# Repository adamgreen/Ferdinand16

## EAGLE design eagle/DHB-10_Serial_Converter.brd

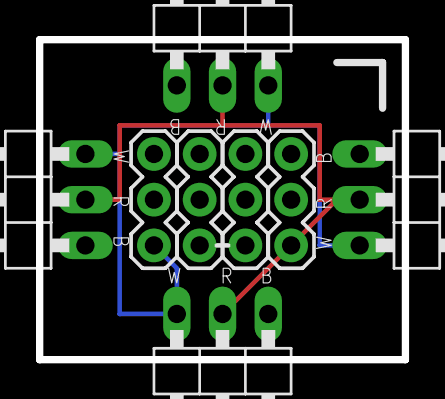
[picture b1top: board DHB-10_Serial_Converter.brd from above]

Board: 2 copper layers, 20.3 x 17.8 mm, 8 parts (0 on the bottom side), 2 nets.

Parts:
E$1, E$6, E$7, E$8: 1X03/90
E$2, E$3, E$4, E$5: 1X03

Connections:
S$1: E$1.3, E$2.1, E$6.3, E$7.3, E$8.3
S$2: E$1.2, E$5.1, E$6.2, E$7.2, E$8.2

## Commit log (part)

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2016-06-03 Initial commit
    * Add gcc4mbed as submodule since my firmware will make use of it.
    * Add initial photos.
    * The picture of the Arlo robot platform comes from the Parallax
    website.
    * The picture of the ESP8266 module comes from the Adafruit website.
2016-06-04 Add photo
    This is the graph of the gyro zero bias versus temperature from 2014.
2016-06-04 Initial README notes
    * Ideas for Robo-Magellan 2016 robot.
    * Initial Pixy camera notes.
    * Re-calibration of roll axis rate gyro in IMU.
2016-06-04 Add gyro calibration spreadhsheet
    This spreadsheet was used to re-calculate the gyro zero bias vs.
    temperature calibration constants.
2016-06-04 Fork orientation sample from Ferdinand14
    Just copying the orientation sample over from the Ferdinand14 project.
    This orientation code uses a Kalman filter to calculate the 3D pose of
    the IMU. I plan to simplify the code to just obtain the compass heading
    and then port to run on the LPC1768 instead of on the PC.
2016-06-06 Adding photos
2016-06-07 June 6th notes
2016-06-08 Add photo of new book
2016-06-09 Add photo of Sparkfun order
2016-06-11 June 10th notes
2016-06-12 Add ESP8266 board photos
2016-06-14 Calculate yaw from quaternion directly
    Previously I was using a row from the rotation matrix (which was
    more expensively obtained from the quaternion) and I now just pull the
    yaw, pitch, and roll angles from the quaternion instead.
2016-06-17 Start porting orientation code to LPC1768
    This is the start of porting the orientation Processing sample to the
    LPC1768. It just starts with porting of the calibration code down to
    the LPC1768 whereas it could only return the raw sensor readings
    previously.
    * The calibration data is found in files/config.ini This file it built
    into a FlashFileSystem image which is then embedded into the firmware
2016-06-18 Calculate orientation quaternion from accelerometer/magnetometer
    This commit switches the firmware to returning an orientation
    quaternion based soley on the accelerometer and magnetometer data.
    Kalman filtering will be added later.
    The orientation Processing sample was modified to expect this
    4 x float quaternion instead of the 9 x float calibrated data I added
    in the previous commit. It compares this quaternion to the one
2016-06-18 Swizzle accel/mag based on config.ini settings
    Previously the swizzling of the accelerometer and magnetometer axis was
    hardcoded. Now it is controlled by parameters in config.ini
    Additional changes include:
    * Added accelSwizzle and magSwizzle field to SensorCalibration struct
    to provide the new swizzle settings to the Sparkfun9DoFSensorStick
    class at construction time.
2016-06-21 Kalman filter ported to LPC1768
    This is the initial port of the Kalman filter from the Processing
    orientation.pde sample running on the PC to C++ code running on the
    LPC1768 microcontroller. The LPC1768 is currently idle for more than
    89% of the time when running this code. This is much better than I
    expected for all of that floating point math and gives me lots of
    headroom to execute my robot navigation code.
2016-06-21 Add Robo-Magellan June 19th photos
    These are photos taken at the June 19th, 2016 Robo-Magellan re-run
    event at Seattle Center.
2016-06-21 June 19th notes
    Notes about the Robo-Magellan 2015 rescheduled event.
2016-06-21 Add some photos
2016-06-21 Add animated GIF of Kalman filter
2016-06-21 June 20th notes
2016-06-22 Commit of quaternion and matrix dumping code
    I just want to keep this code around incase I want to reference it in
    the future. It is able to dump floats from various Kalman quaternions
    and matrices right after the filter is reset to compare the values
    between the PC and LPC1768.
    NOTE: It does contain a few fixes which I will port back into master as
    well.
2016-06-22 Kalman filter fixes
    * Make the Kalman filter reset a thread safe. Before it was possible
    for the code in main() which would trigger the Kalman filter
    to reset and the code which would prepend the "R," to the output
    would see different values of the g_resetRequested global that is
    set true in the serialRx ISR.
    * Sparkfun9DoFSensorStick::calibrate() gyroVariance & accelMagVariance
2016-06-23 PC and LPC1768 now agree on Kalman filter results
    I was normalizing the quaternion on the LPC1768 but not the PC. This is
    now fixed.
    I also fixed the code so that it only compares the embedded results
    after the reset has completed.
    Now get no differences detected when using a threshold of 1.0E-5.
2016-06-24 Add photo of Arlo
2016-06-25 June 24th notes
2016-06-28 June 28th notes
2016-07-12 July 11th notes
2016-07-12 Update README
    I wanted to make my comment about the 11% CPU utilization clearer. This
    was much better than I expected to obtain when I started the port.
2016-07-14 Commit some Parallax Arlo documentation
    * Documents for the DHB-10 Dual 10-Amp Motor Controller used on the
    Arlo robot platform for this Robo-Magellan bot. The LPC1768 will need
    to be interfaced to this motor controller in the near future.
    * The schematic for the power distribution board on the Arlo.
2016-07-14 Update compass/heading rendering
    I moved the code to calculate the compass heading from orientation.pde
    to HeadingSensor.pde This code was then updated to:
    * Return a heading angle of 0 when the robot is facing north.
    * Return a heading angle of PI/2 when the robot is facing east and
    an angle of -PI/2 when facing west.
    * Add configuration options to calibrate for the magnetic declination
2016-07-15 Start IMU firmware up in mode compatible with old samples
    The old Ferdinand14 samples like the ones I have for performing sensor
    calibration only expect the raw sensor readings. I have modified the
    firmware running on the LPC1768 to startup in a mode which only returns
    these raw sensor measurements and only starts returning the Kalman
    calculated values after a Kalman reset command has been sent from the
    PC.
2016-07-19 July 18th notes
2016-07-19 Move firmware & Processing code into sub-folders
    To support more than one Processing sample and firmware image for this
    project, there are now processing/ and firmware/ parent folders. The
    multiple Processing samples can be placed under processing/ and the
    different firmware images can be placed under firmware/.
    I also added the mriprog utility for OSX under the osx/ folder. This
    utility can be used to remotely program a LPC1768 device which is
2016-07-19 Build DmaSerial as a library
    I want to share the DmaSerial functionality between the basic heading
    firmware that I have been working on so far and the other firmware
    variants that I plan to create in the future. To facilitate this, I
    have moved the DMA code out into its own libs/DmaSerial directory. I
    also replaced DMA.h with GPDMA.h/c from my NeoPixelTree project where
    I added GPDMA channel allocation functionality. This will allow me to
2016-07-20 Add simple drive sample
    This sample instructs the Arlo platform to drive ahead at a speed of
    100 encoder ticks per second and verifies that the overall distance
    travelled (in encoder ticks) has increased as expected. This test is
    run for 2 seconds and then the robot is stopped.
    The bulk of the functionality is provided by the newly added
    libs/MotorController library which knows how to talk to the Parallax
2016-07-20 Add photos of completed Arlo build
    With Propeller board as the brains and another with the mbed LPC1768 as
    the brains.
2016-07-23 Move orientation sensor code into libraries
    I have moved the Sparkfun9DoFSensorStick code out into its own library
    so that it can be shared by the current Heading firmware and the new
    firmware for the robot itself. I also moved ConfigFile and
    FlashFileSystem out into their own libraries as well.
2016-07-23 Add photo
    Shows electronics to be combined inside of prototyping box.
2016-07-23 Add photo of merged electronics
2016-07-23 Add IMU sensor documentation
2016-07-23 Initial Ferdinand16 schematic
    I created a schematic in Eagle CAD to provide an overview of what
    electronics I am currently using for the brains of my Ferdinand16
    project.
2016-07-24 Add DHB-10 serial converter board layout
    I used Eagle CAD to create a PCB layout for a board which attaches to
    the I/O pins on the Parallax DHB-10 Dual Motor Controller and allows
    the user to utilize a 3-wire servo cable for full-duplex serial
    communication. Once mounted on the 3x4 DHB-10 I/O header, the user
    can connect their 3-wire servo cable to one of the 90 degree 3-pin
    headers along the perimeter of the board.
2016-07-26 July 25th notes
2016-07-27 Re-calibrate heading sensor after mounting on robot
    The magnetometer calibration data had to be updated to account for hard
    iron on the robot. I also adjusted the compass.mountingCorrection to
    account for the fact that I mounted the project box 180 degrees from
    the original orientation. The USB connector now points towards the
    front of the robot and not the back.
2016-07-28 Move GPDMA into its own library
    Previously the GPDMA source files were located in the DmaSerial
    library. Moving it out into its own library so that it can be used
    by modules other than DmaSerial by future commits.
2016-07-28 Fix typo in ConfigFile.cpp
    I just noticed and corrected a typo in a comment while reviewing this
    code recently.
2016-07-28 Update mriprog utility
    I modified mriprog so that the second stage bootloader finds the MRI
    UART by searching for the UART ISR with the highest priority.
    Previously it expected it to have the highest priority (level 0) but I
    have an upcoming commit which sets it to one level below this.
2016-07-28 Add DebugSerial library/class
    This class can be used to extend the functionality of the MRI debug
    monitor. In particular, it allows for the sending of debug output to
    GDB in an async fashion without blocking the CPU. Without this class
    output is sent to the GDB console using printf() which ends up
    halting into the MRI debug monitor to start a dialog with GDB and it
    remains halted until all of the text has been sent to GDB. When a
2016-07-28 Initial Robo-Magellan robot firmware
    This code doesn't really do much at this point. It does pull in the
    Sparkfun9DoFSensorStick and MotorController classes that will be needed
    by the robot for initial navigation tests. It also has the start of the
    debugging framework that I plan to use.
    It takes advantage of the DebugSerial class for sending messages to the
    GDB console in an asynchronous fashion to minimize the impact on
2016-07-28 Add photo of mounted project box
2016-07-29 Rotate robot inplace for PID modelling
    The robot firmware now runs in a mode where it oscillates back and
    forth 90 degrees around its original orientation. While doing this
    oscillation it logs the time, current heading angle from the
    orientation sensor, and the control output being sent to the motors.
    Issuing the "set logging on" command to GDB before starting this test
    will cause the logged data to be recorded in gdb.txt. I then edit
2016-07-30 Add photo of WiFi router
2016-07-30 Photo of first outdoor run
2016-08-14 August 14th notes
2016-09-30 Photos of serial converter PCB
2016-09-30 Add photos
2016-09-30 Add SRS logo image
    This image was moved around on the SRS Robothon site after a recent
    site update so I will just pull it into this project to make sure
    that the link doesn't break again in the future.
2016-09-30 September 29th notes
2016-10-05 Add photos of Robomagellan 2016
2016-10-05 October 4th notes

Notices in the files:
eagle/DHB-10_Serial_Converter.brd:
CC-BY-SA
parts and their libraries:
SparkFun-Capacitors: Licensing: Creative Commons ShareAlike 4.0 International - https://creativecommons.org/licenses/by-sa/4.0
